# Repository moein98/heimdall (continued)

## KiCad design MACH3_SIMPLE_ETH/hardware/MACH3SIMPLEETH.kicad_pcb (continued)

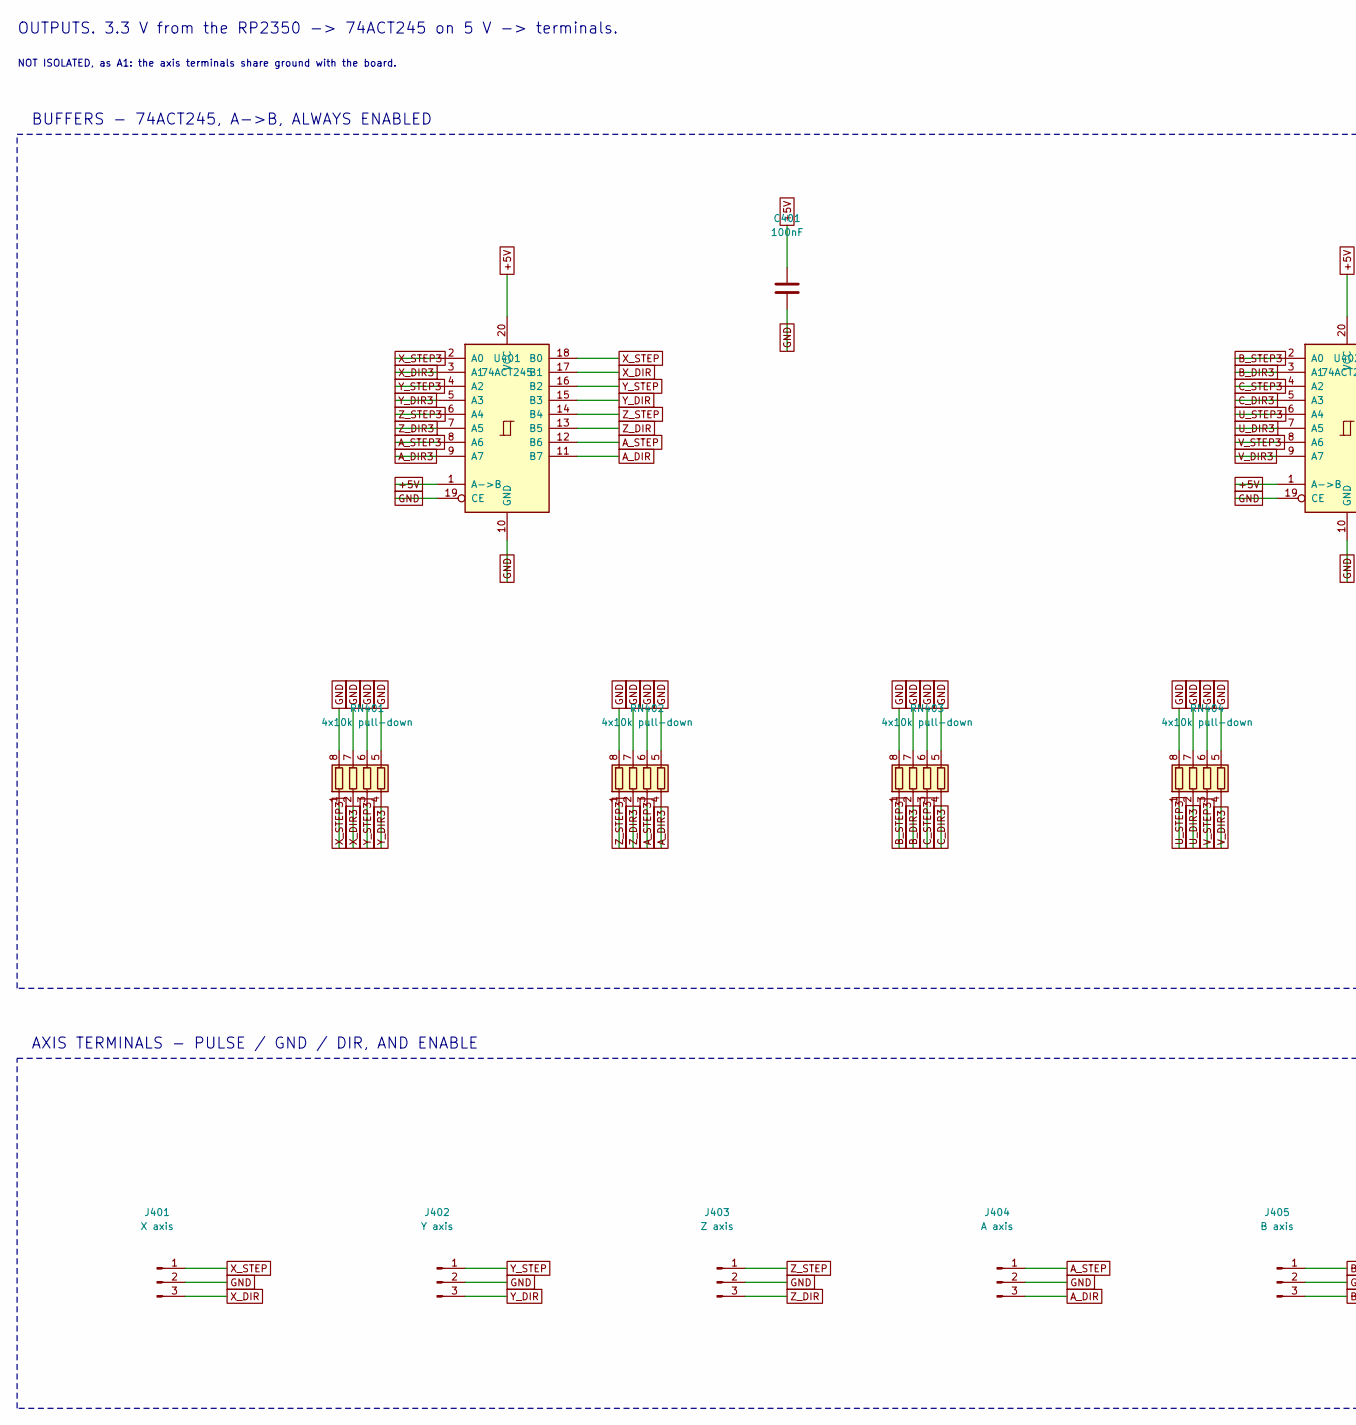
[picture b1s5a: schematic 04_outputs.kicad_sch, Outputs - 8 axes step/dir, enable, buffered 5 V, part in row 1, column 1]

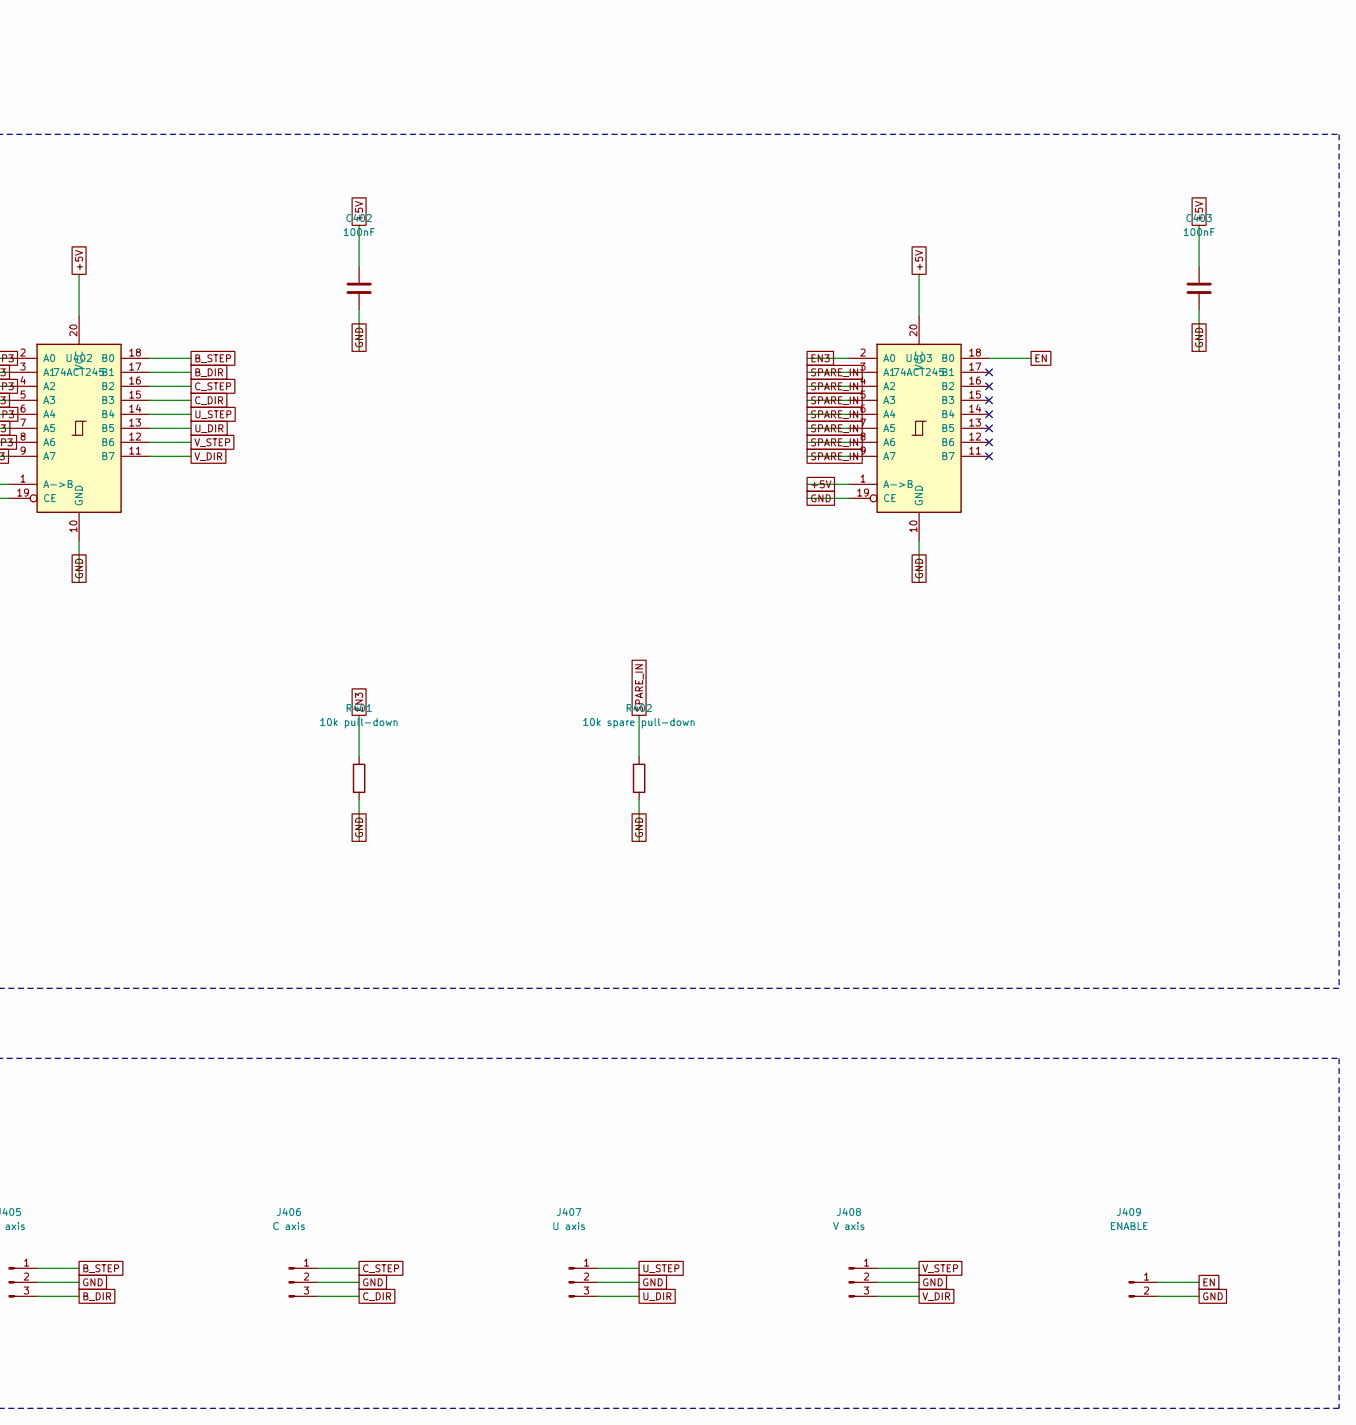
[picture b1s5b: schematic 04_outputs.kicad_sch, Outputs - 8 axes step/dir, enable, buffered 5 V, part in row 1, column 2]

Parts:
C401, C402, C403: 100nF; C_0603_1608Metric
J401: X axis; TerminalBlock_Phoenix_MKDS-1,5-3_1x03_P5.00mm_Horizontal
J402: Y axis; TerminalBlock_Phoenix_MKDS-1,5-3_1x03_P5.00mm_Horizontal
J403: Z axis; TerminalBlock_Phoenix_MKDS-1,5-3_1x03_P5.00mm_Horizontal
J404: A axis; TerminalBlock_Phoenix_MKDS-1,5-3_1x03_P5.00mm_Horizontal
J405: B axis; TerminalBlock_Phoenix_MKDS-1,5-3_1x03_P5.00mm_Horizontal
J406: C axis; TerminalBlock_Phoenix_MKDS-1,5-3_1x03_P5.00mm_Horizontal
J407: U axis; TerminalBlock_Phoenix_MKDS-1,5-3_1x03_P5.00mm_Horizontal
J408: V axis; TerminalBlock_Phoenix_MKDS-1,5-3_1x03_P5.00mm_Horizontal
J409: ENABLE; TerminalBlock_Phoenix_MKDS-1,5-2_1x02_P5.00mm_Horizontal
R401: 10k pull-down; R_0603_1608Metric
R402: 10k spare pull-down; R_0603_1608Metric
RN401, RN402, RN403, RN404: 4x10k pull-down; R_Array_Convex_4x0603
U401, U402, U403: 74ACT245; SOIC-20W_7.5x12.8mm_P1.27mm

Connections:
+5V: C401.1, C402.1, C403.1, U401.1 (A->B), U401.20 (VCC), U402.1 (A->B), U402.20 (VCC), U403.1 (A->B), U403.20 (VCC); also elsewhere on the board
A_DIR: J404.3, U401.11 (B7)
A_DIR3: RN402.4 (R4.1), U401.9 (A7); also elsewhere on the board
A_STEP: J404.1, U401.12 (B6)
A_STEP3: RN402.3 (R3.1), U401.8 (A6); also elsewhere on the board
B_DIR: J405.3, U402.17 (B1)
B_DIR3: RN403.2 (R2.1), U402.3 (A1); also elsewhere on the board
B_STEP: J405.1, U402.18 (B0)
B_STEP3: RN403.1 (R1.1), U402.2 (A0); also elsewhere on the board
C_DIR: J406.3, U402.15 (B3)
C_DIR3: RN403.4 (R4.1), U402.5 (A3); also elsewhere on the board
C_STEP: J406.1, U402.16 (B2)
C_STEP3: RN403.3 (R3.1), U402.4 (A2); also elsewhere on the board
EN: J409.1, U403.18 (B0)
EN3: R401.1, U403.2 (A0); also elsewhere on the board
GND: C401.2, C402.2, C403.2, J401.2, J402.2, J403.2, J404.2, J405.2, J406.2, J407.2, J408.2, J409.2, R401.2, R402.2, RN401.5 (R4.2), RN401.6 (R3.2), RN401.7 (R2.2), RN401.8 (R1.2), RN402.5 (R4.2), RN402.6 (R3.2), RN402.7 (R2.2), RN402.8 (R1.2), RN403.5 (R4.2), RN403.6 (R3.2), RN403.7 (R2.2), RN403.8 (R1.2), RN404.5 (R4.2), RN404.6 (R3.2), RN404.7 (R2.2), RN404.8 (R1.2), U401.10 (GND), U401.19 (CE), U402.10 (GND), U402.19 (CE), U403.10 (GND), U403.19 (CE); also elsewhere on the board
SPARE_IN: R402.1, U403.3 (A1), U403.4 (A2), U403.5 (A3), U403.6 (A4), U403.7 (A5), U403.8 (A6), U403.9 (A7)
U_DIR: J407.3, U402.13 (B5)
U_DIR3: RN404.2 (R2.1), U402.7 (A5); also elsewhere on the board
U_STEP: J407.1, U402.14 (B4)
U_STEP3: RN404.1 (R1.1), U402.6 (A4); also elsewhere on the board
V_DIR: J408.3, U402.11 (B7)
V_DIR3: RN404.4 (R4.1), U402.9 (A7); also elsewhere on the board
V_STEP: J408.1, U402.12 (B6)
V_STEP3: RN404.3 (R3.1), U402.8 (A6); also elsewhere on the board
X_DIR: J401.3, U401.17 (B1)
X_DIR3: RN401.2 (R2.1), U401.3 (A1); also elsewhere on the board
X_STEP: J401.1, U401.18 (B0)
X_STEP3: RN401.1 (R1.1), U401.2 (A0); also elsewhere on the board
Y_DIR: J402.3, U401.15 (B3)
Y_DIR3: RN401.4 (R4.1), U401.5 (A3); also elsewhere on the board
Y_STEP: J402.1, U401.16 (B2)
Y_STEP3: RN401.3 (R3.1), U401.4 (A2); also elsewhere on the board
Z_DIR: J403.3, U401.13 (B5)
Z_DIR3: RN402.2 (R2.1), U401.7 (A5); also elsewhere on the board
Z_STEP: J403.1, U401.14 (B4)
Z_STEP3: RN402.1 (R1.1), U401.6 (A4); also elsewhere on the board

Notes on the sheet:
OUTPUTS. 3.3 V from the RP2350 -> 74ACT245 on 5 V -> terminals.
NOT ISOLATED, as A1: the axis terminals share ground with the board.
BUFFERS - 74ACT245, A->B, ALWAYS ENABLED
AXIS TERMINALS - PULSE / GND / DIR, AND ENABLE

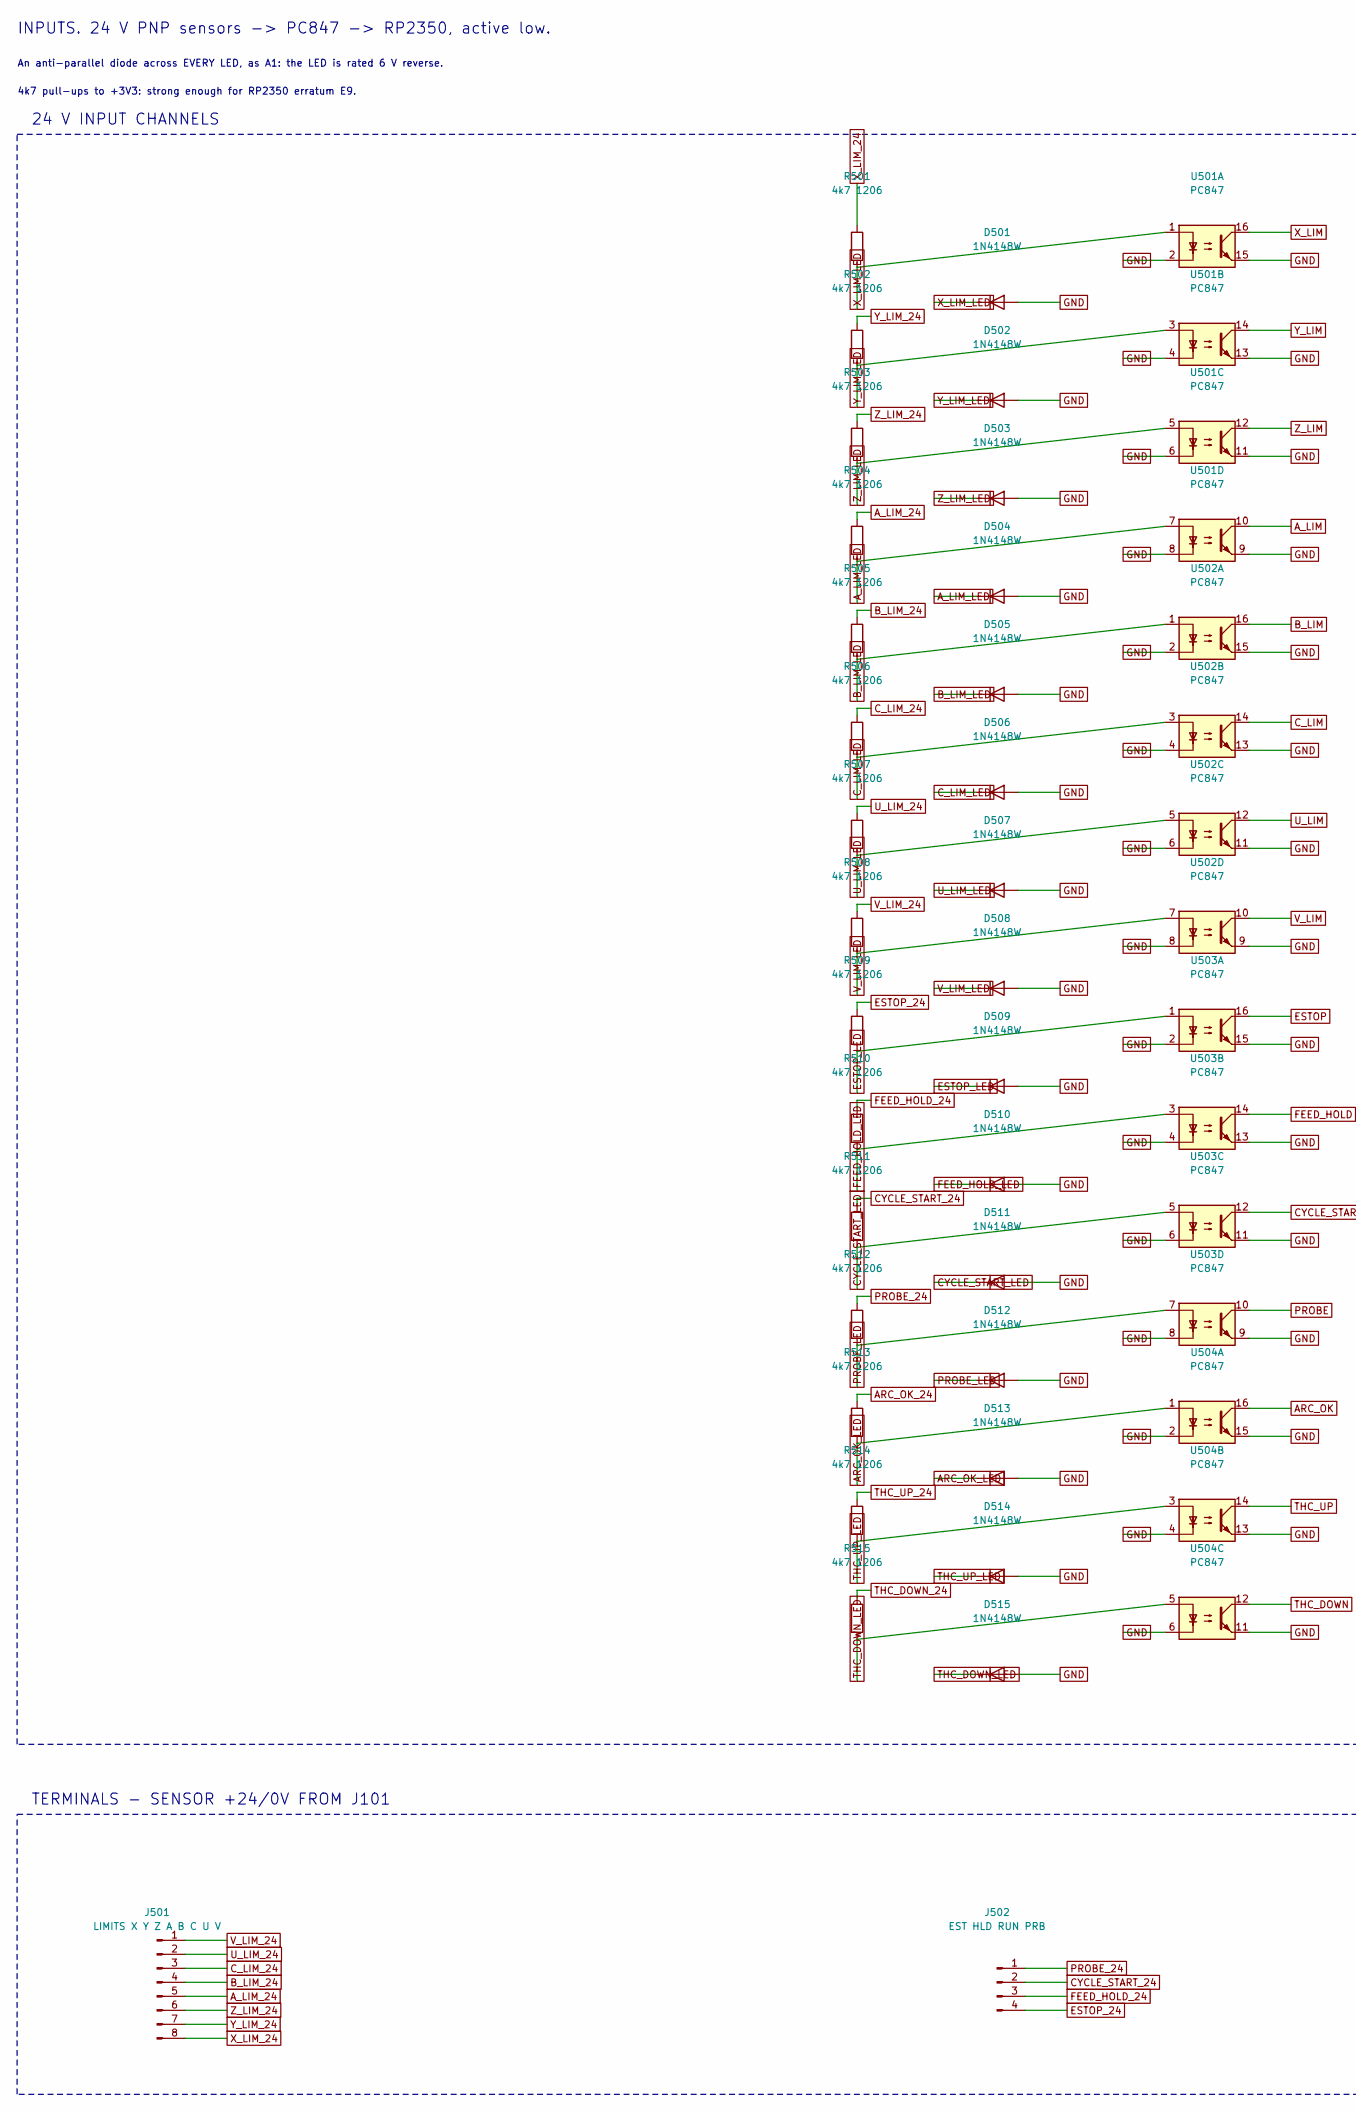
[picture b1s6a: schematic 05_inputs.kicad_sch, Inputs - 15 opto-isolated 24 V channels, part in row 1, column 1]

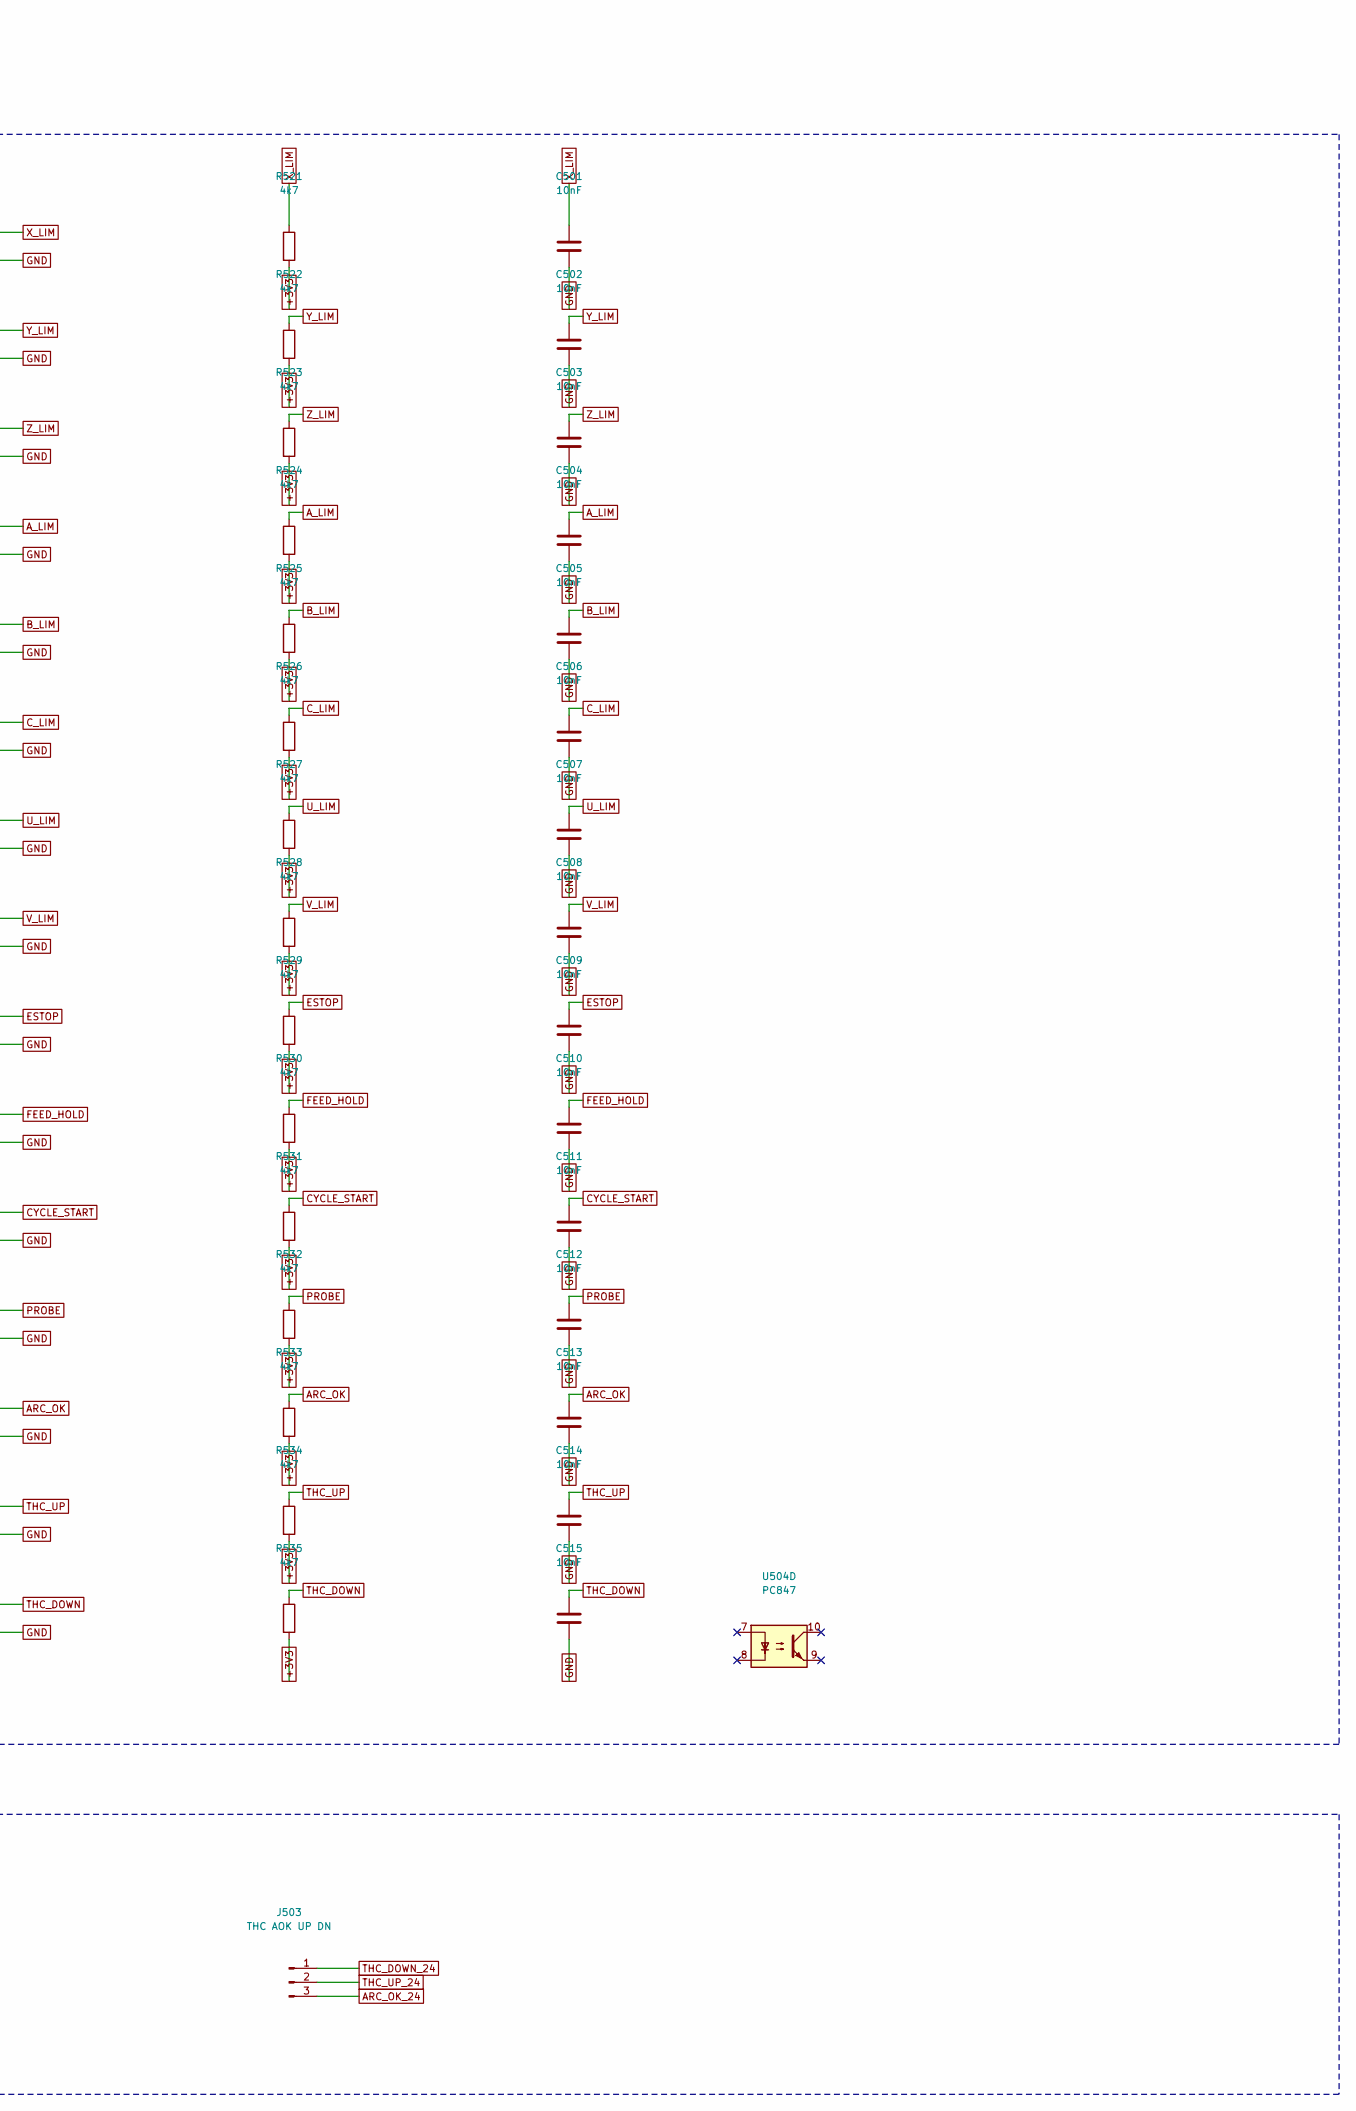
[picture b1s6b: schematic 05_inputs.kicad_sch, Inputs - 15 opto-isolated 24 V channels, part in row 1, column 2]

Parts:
C501, C502, C503, C504, C505, C506, C507, C508, C509, C510, C511, C512, C513, C514, C515: 10nF; C_0603_1608Metric
D501, D502, D503, D504, D505, D506, D507, D508, D509, D510, D511, D512, D513, D514, D515: 1N4148W; D_SOD-123
J501: LIMITS X Y Z A B C U V; TerminalBlock_Phoenix_MKDS-1,5-8_1x08_P5.00mm_Horizontal
J502: EST HLD RUN PRB; TerminalBlock_Phoenix_MKDS-1,5-4_1x04_P5.00mm_Horizontal
J503: THC AOK UP DN; TerminalBlock_Phoenix_MKDS-1,5-3_1x03_P5.00mm_Horizontal
R501, R502, R503, R504, R505, R506, R507, R508, R509, R510, R511, R512, R513, R514, R515: 4k7 1206; R_1206_3216Metric
R521, R522, R523, R524, R525, R526, R527, R528, R529, R530, R531, R532, R533, R534, R535: 4k7; R_0603_1608Metric
U501, U502, U503, U504: PC847; SMDIP-16_W9.53mm

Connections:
+3V3: R521.2, R522.2, R523.2, R524.2, R525.2, R526.2, R527.2, R528.2, R529.2, R530.2, R531.2, R532.2, R533.2, R534.2, R535.2; also elsewhere on the board
ARC_OK: C513.1, R533.1, U504.16; also elsewhere on the board
ARC_OK_24: J503.3, R513.1
ARC_OK_LED: D513.1 (K), R513.2, U504.1
A_LIM: C504.1, R524.1, U501.10; also elsewhere on the board
A_LIM_24: J501.5, R504.1
A_LIM_LED: D504.1 (K), R504.2, U501.7
B_LIM: C505.1, R525.1, U502.16; also elsewhere on the board
B_LIM_24: J501.4, R505.1
B_LIM_LED: D505.1 (K), R505.2, U502.1
CYCLE_START: C511.1, R531.1, U503.12; also elsewhere on the board
CYCLE_START_24: J502.2, R511.1
CYCLE_START_LED: D511.1 (K), R511.2, U503.5
C_LIM: C506.1, R526.1, U502.14; also elsewhere on the board
C_LIM_24: J501.3, R506.1
C_LIM_LED: D506.1 (K), R506.2, U502.3
ESTOP: C509.1, R529.1, U503.16; also elsewhere on the board
ESTOP_24: J502.4, R509.1
ESTOP_LED: D509.1 (K), R509.2, U503.1
FEED_HOLD: C510.1, R530.1, U503.14; also elsewhere on the board
FEED_HOLD_24: J502.3, R510.1
FEED_HOLD_LED: D510.1 (K), R510.2, U503.3
GND: C501.2, C502.2, C503.2, C504.2, C505.2, C506.2, C507.2, C508.2, C509.2, C510.2, C511.2, C512.2, C513.2, C514.2, C515.2, D501.2 (A), D502.2 (A), D503.2 (A), D504.2 (A), D505.2 (A), D506.2 (A), D507.2 (A), D508.2 (A), D509.2 (A), D510.2 (A), D511.2 (A), D512.2 (A), D513.2 (A), D514.2 (A), D515.2 (A), U501.2, U501.4, U501.6, U501.8, U501.9, U501.11, U501.13, U501.15, U502.2, U502.4, U502.6, U502.8, U502.9, U502.11, U502.13, U502.15, U503.2, U503.4, U503.6, U503.8, U503.9, U503.11, U503.13, U503.15, U504.2, U504.4, U504.6, U504.11, U504.13, U504.15; also elsewhere on the board
PROBE: C512.1, R532.1, U503.10; also elsewhere on the board
PROBE_24: J502.1, R512.1
PROBE_LED: D512.1 (K), R512.2, U503.7
THC_DOWN: C515.1, R535.1, U504.12; also elsewhere on the board
THC_DOWN_24: J503.1, R515.1
THC_DOWN_LED: D515.1 (K), R515.2, U504.5
THC_UP: C514.1, R534.1, U504.14; also elsewhere on the board
THC_UP_24: J503.2, R514.1
THC_UP_LED: D514.1 (K), R514.2, U504.3
U_LIM: C507.1, R527.1, U502.12; also elsewhere on the board
U_LIM_24: J501.2, R507.1
U_LIM_LED: D507.1 (K), R507.2, U502.5
V_LIM: C508.1, R528.1, U502.10; also elsewhere on the board
V_LIM_24: J501.1, R508.1
V_LIM_LED: D508.1 (K), R508.2, U502.7
X_LIM: C501.1, R521.1, U501.16; also elsewhere on the board
X_LIM_24: J501.8, R501.1
X_LIM_LED: D501.1 (K), R501.2, U501.1
Y_LIM: C502.1, R522.1, U501.14; also elsewhere on the board
Y_LIM_24: J501.7, R502.1
Y_LIM_LED: D502.1 (K), R502.2, U501.3
Z_LIM: C503.1, R523.1, U501.12; also elsewhere on the board
Z_LIM_24: J501.6, R503.1
Z_LIM_LED: D503.1 (K), R503.2, U501.5

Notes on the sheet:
INPUTS. 24 V PNP sensors -> PC847 -> RP2350, active low.
An anti-parallel diode across EVERY LED, as A1: the LED is rated 6 V reverse.
4k7 pull-ups to +3V3: strong enough for RP2350 erratum E9.
24 V INPUT CHANNELS
TERMINALS - SENSOR +24/0V FROM J101

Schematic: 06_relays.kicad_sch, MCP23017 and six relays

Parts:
C601: 100nF; C_0603_1608Metric
D601: STATUS; LED_0603_1608Metric
D611, D612, D613, D614, D615, D616: 1N4148W flyback; D_SOD-123
D621: KA; LED_0603_1608Metric
D622: KB; LED_0603_1608Metric
D623: KC; LED_0603_1608Metric
D624: KD; LED_0603_1608Metric
D625: KE; LED_0603_1608Metric
D626: KF; LED_0603_1608Metric
J601: EXPANSION; IDC-Header_2x05_P2.54mm_Vertical
J611: Relay A; TerminalBlock_Phoenix_MKDS-1,5-3_1x03_P5.00mm_Horizontal
J612: Relay B; TerminalBlock_Phoenix_MKDS-1,5-3_1x03_P5.00mm_Horizontal
J613: Relay C; TerminalBlock_Phoenix_MKDS-1,5-3_1x03_P5.00mm_Horizontal
J614: Relay D; TerminalBlock_Phoenix_MKDS-1,5-3_1x03_P5.00mm_Horizontal
J615: Relay E; TerminalBlock_Phoenix_MKDS-1,5-3_1x03_P5.00mm_Horizontal
J616: Relay F; TerminalBlock_Phoenix_MKDS-1,5-3_1x03_P5.00mm_Horizontal
K601, K602, K603, K604, K605, K606: JQC-3FF-024-1Z; Relay_SPDT_Hongfa_JQC-3FF_0XX-1Z
Q601, Q602, Q603, Q604, Q605, Q606: AO3400A; SOT-23
R601, R602: 4.7k; R_0603_1608Metric
R603, R621, R622, R623, R624, R625, R626: 1k; R_0603_1608Metric
R604, R605, R606, R607, R608, R609, R610, R611, R631, R632, R633, R634, R635, R636, R641, R642, R643, R644, R645, R646: 10k; R_0603_1608Metric
U601: MCP23017-E/SO; SOIC-28W_7.5x17.9mm_P1.27mm

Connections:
+3V3: C601.1, J601.9, R601.1, R602.1, R604.2, R605.2, R606.2, R607.2, R608.2, R609.2, R610.2, R611.2, U601.9 (V_{DD}); also elsewhere on the board
EXP_IN0: J601.1, R604.1, U601.1 (GPB0)
EXP_IN1: J601.2, R605.1, U601.2 (GPB1)
EXP_IN2: J601.3, R606.1, U601.3 (GPB2)
EXP_IN3: J601.4, R607.1, U601.4 (GPB3)
EXP_IN4: J601.5, R608.1, U601.5 (GPB4)
EXP_IN5: J601.6, R609.1, U601.6 (GPB5)
EXP_IN6: J601.7, R610.1, U601.7 (GPB6)
EXP_IN7: J601.8, R611.1, U601.8 (GPB7)
GND: C601.2, D601.1 (K), J601.10, Q601.2 (S), Q602.2 (S), Q603.2 (S), Q604.2 (S), Q605.2 (S), Q606.2 (S), R631.2, R632.2, R633.2, R634.2, R635.2, R636.2, U601.10 (V_{SS}), U601.15 (A0), U601.16 (A1), U601.17 (A2); also elsewhere on the board
I2C_SCL: R602.2, U601.12 (SCK); also elsewhere on the board
I2C_SDA: R601.2, U601.13 (SDA); also elsewhere on the board
KA_COM: J611.2, K601.11
KA_NC: J611.3, K601.12
KA_NO: J611.1, K601.14
KB_COM: J612.2, K602.11
KB_NC: J612.3, K602.12
KB_NO: J612.1, K602.14
KC_COM: J613.2, K603.11
KC_NC: J613.3, K603.12
KC_NO: J613.1, K603.14
KD_COM: J614.2, K604.11
KD_NC: J614.3, K604.12
KD_NO: J614.1, K604.14
KE_COM: J615.2, K605.11
KE_NC: J615.3, K605.12
KE_NO: J615.1, K605.14
KF_COM: J616.2, K606.11
KF_NC: J616.3, K606.12
KF_NO: J616.1, K606.14
NRST: U601.18 (~RESET); also elsewhere on the board
unnamed: D621.2 (A), R641.2
unnamed: D622.2 (A), R642.2
unnamed: D623.2 (A), R643.2
unnamed: D624.2 (A), R644.2
unnamed: D625.2 (A), R645.2
unnamed: D626.2 (A), R646.2
unnamed: Q601.1 (G), R621.2
unnamed: Q602.1 (G), R622.2
unnamed: Q603.1 (G), R623.2
unnamed: Q604.1 (G), R624.2
unnamed: Q605.1 (G), R625.2
unnamed: Q606.1 (G), R626.2
RELC_A: D611.2 (A), D621.1 (K), K601.A2, Q601.3 (D)
RELC_B: D612.2 (A), D622.1 (K), K602.A2, Q602.3 (D)
RELC_C: D613.2 (A), D623.1 (K), K603.A2, Q603.3 (D)
RELC_D: D614.2 (A), D624.1 (K), K604.A2, Q604.3 (D)
RELC_E: D615.2 (A), D625.1 (K), K605.A2, Q605.3 (D)
RELC_F: D616.2 (A), D626.1 (K), K606.A2, Q606.3 (D)
REL_A: R621.1, R631.1, U601.21 (GPA0)
REL_B: R622.1, R632.1, U601.22 (GPA1)
REL_C: R623.1, R633.1, U601.23 (GPA2)
REL_D: R624.1, R634.1, U601.24 (GPA3)
REL_E: R625.1, R635.1, U601.25 (GPA4)
REL_F: R626.1, R636.1, U601.26 (GPA5)
SP_AUX_IN: U601.27 (GPA6); also elsewhere on the board
STATUS_LED: R603.1, U601.28 (GPA7)
STATUS_LED_A: D601.2 (A), R603.2
V24: D611.1 (K), D612.1 (K), D613.1 (K), D614.1 (K), D615.1 (K), D616.1 (K), K601.A1, K602.A1, K603.A1, K604.A1, K605.A1, K606.A1, R641.1, R642.1, R643.1, R644.1, R645.1, R646.1; also elsewhere on the board

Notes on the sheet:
RELAYS. MCP23017 (I2C 0x20) -> AO3400A -> 24 V relay coils.
G-code M62/M63 P<n> switch them, synchronised with motion; M64/M65 at once.
MCP23017 AND EXPANSION HEADER
SIX RELAYS - 24 V COILS ONLY, AS A1

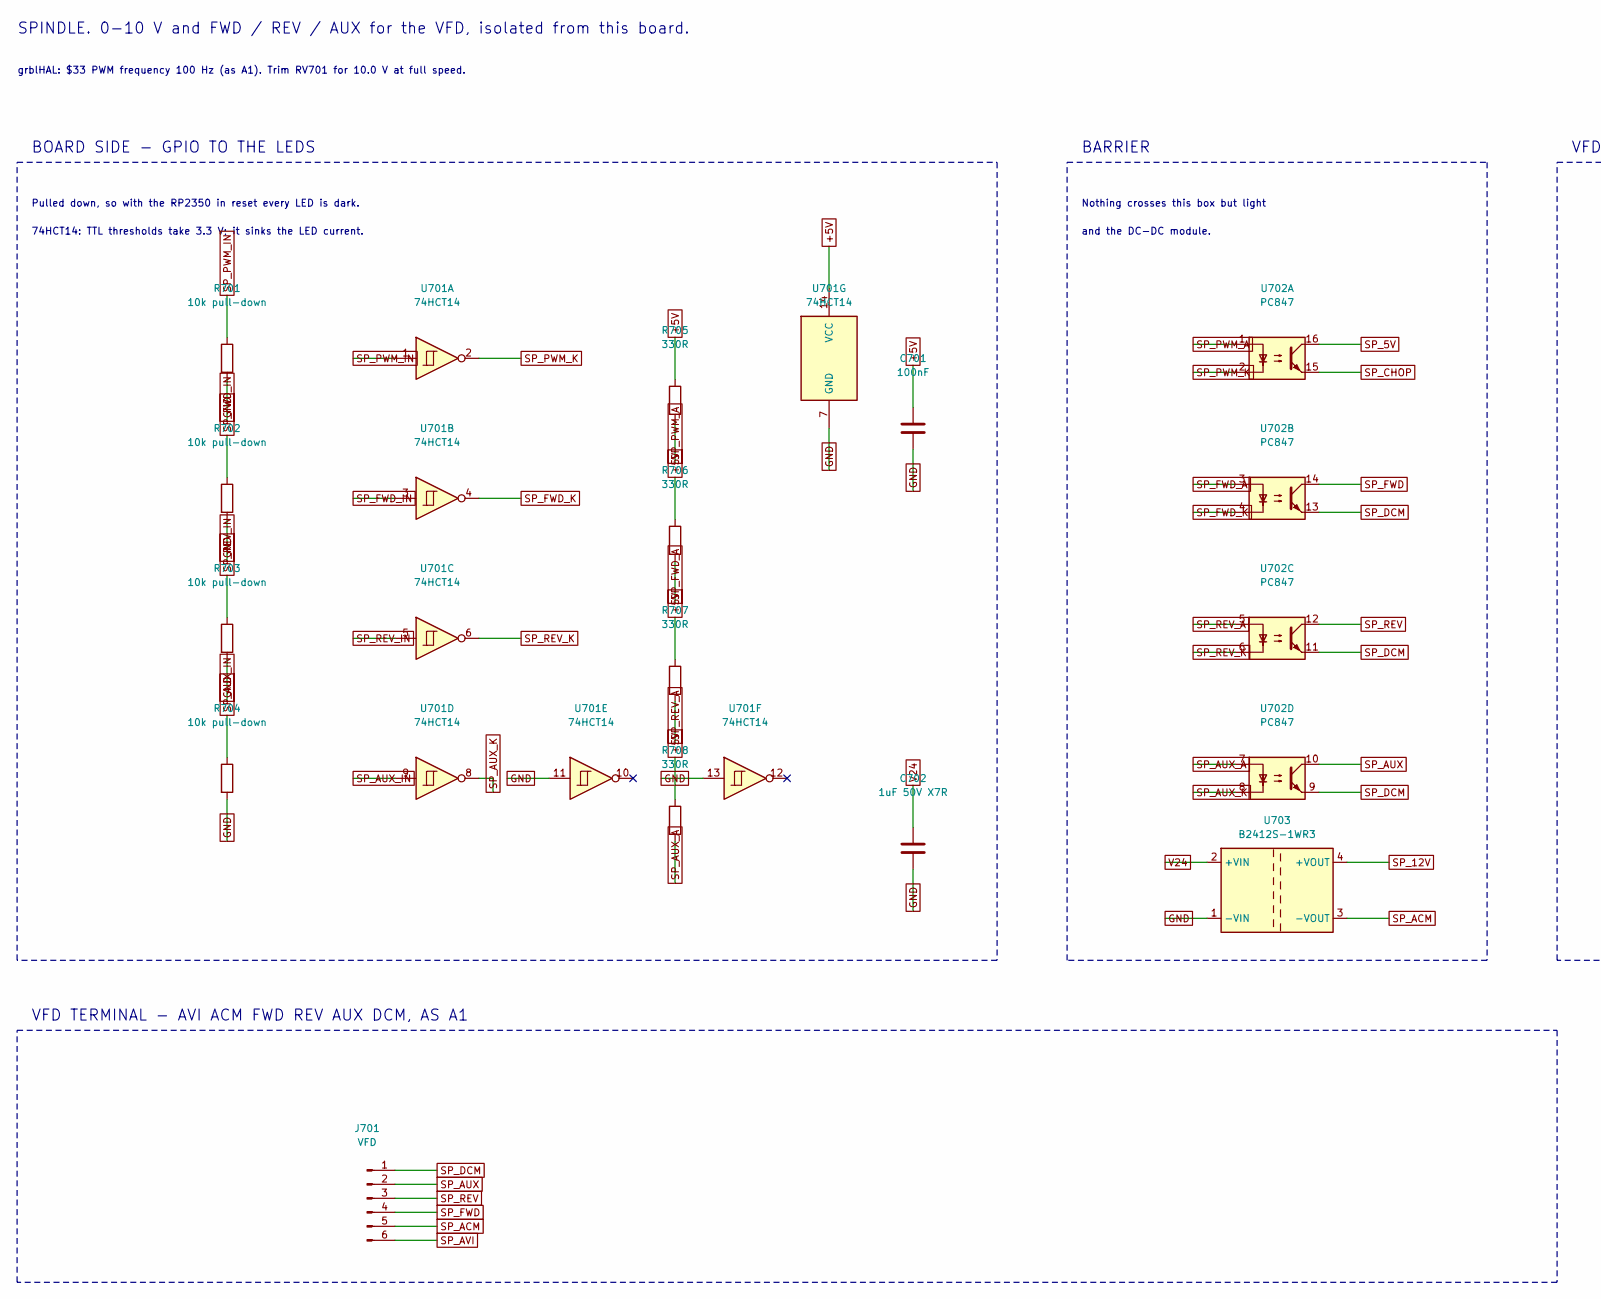
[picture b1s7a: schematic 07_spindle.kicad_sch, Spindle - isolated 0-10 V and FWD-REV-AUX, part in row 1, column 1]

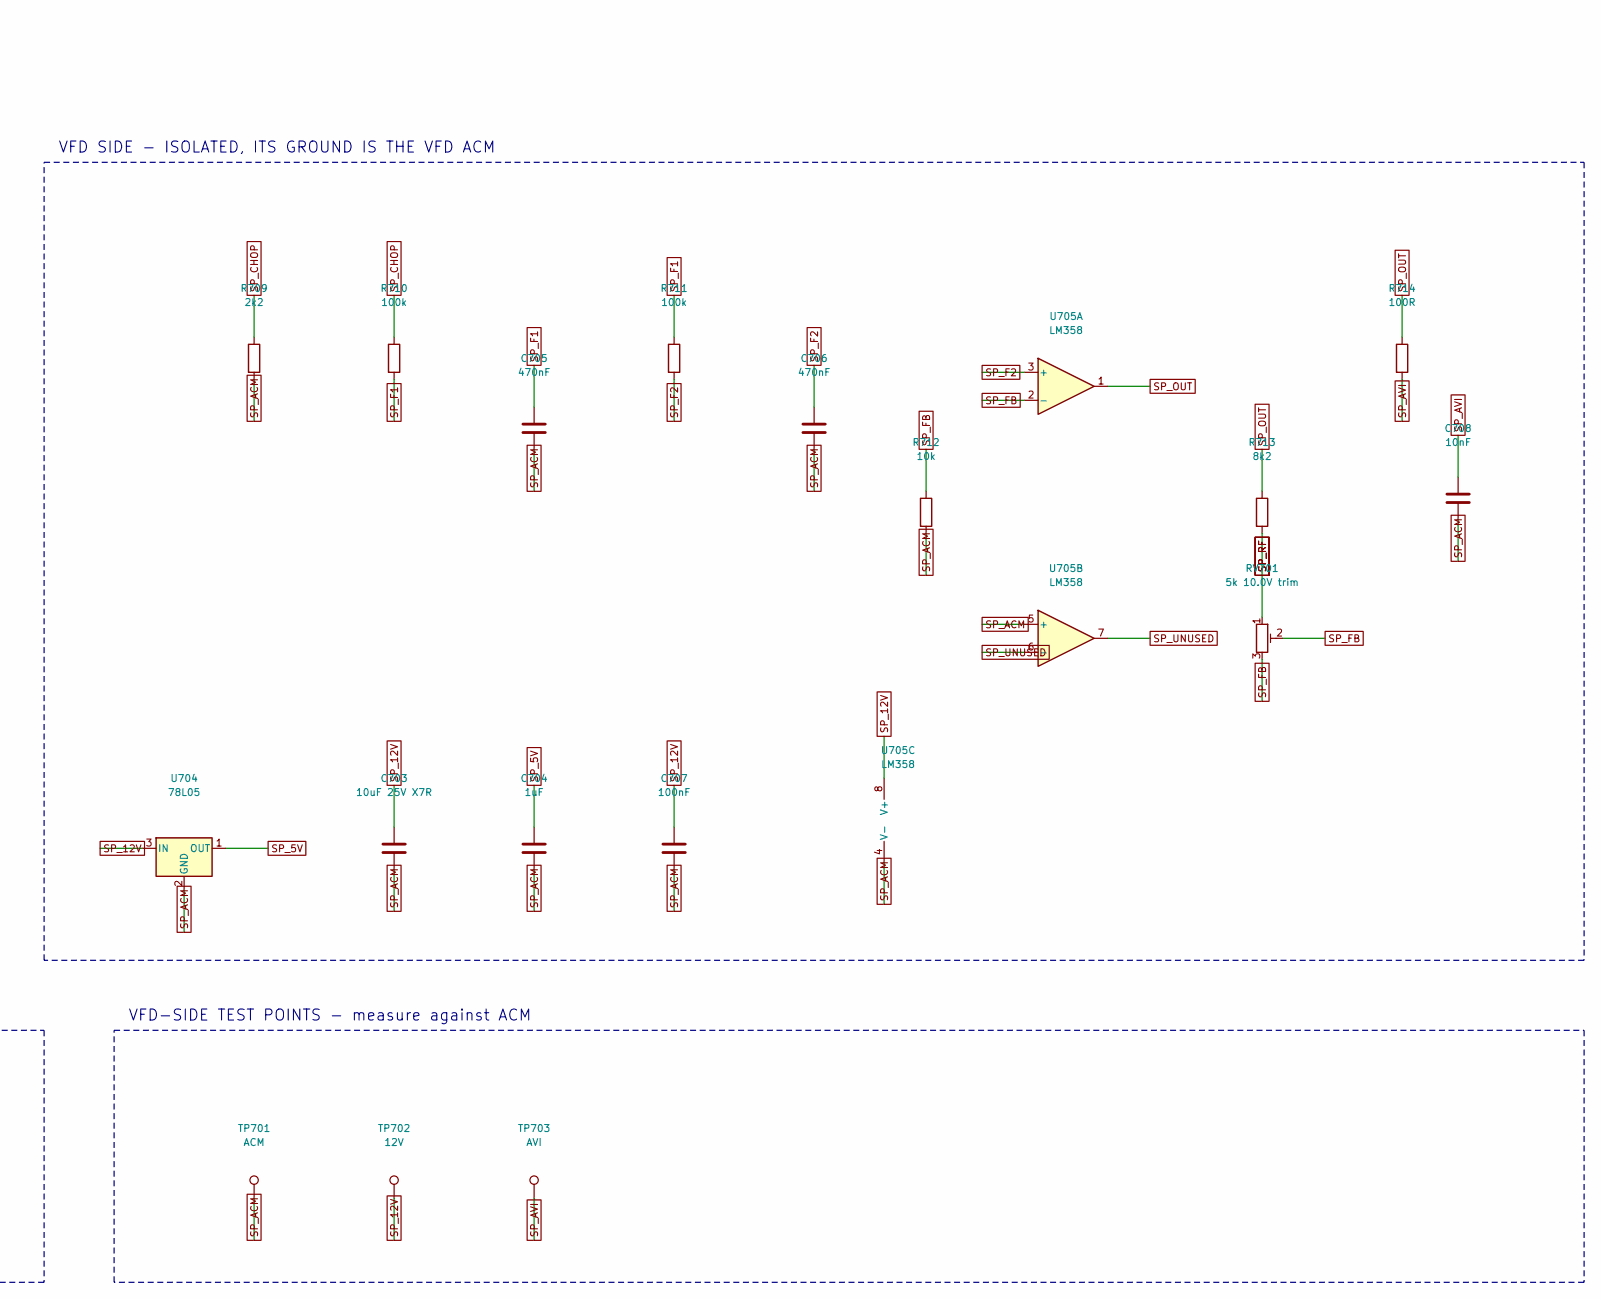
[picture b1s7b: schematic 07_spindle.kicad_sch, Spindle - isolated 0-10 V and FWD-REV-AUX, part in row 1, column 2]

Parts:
C701, C707: 100nF; C_0603_1608Metric
C702: 1uF 50V X7R; C_1206_3216Metric
C703: 10uF 25V X7R; C_1206_3216Metric
C704: 1uF; C_0603_1608Metric
C705, C706: 470nF; C_0603_1608Metric
C708: 10nF; C_0603_1608Metric
J701: VFD; TerminalBlock_Phoenix_MKDS-1,5-6_1x06_P5.00mm_Horizontal
R701, R702, R703, R704: 10k pull-down; R_0603_1608Metric
R705, R706, R707, R708: 330R; R_0603_1608Metric
R709: 2k2; R_0603_1608Metric
R710, R711: 100k; R_0603_1608Metric
R712: 10k; R_0603_1608Metric
R713: 8k2; R_0603_1608Metric
R714: 100R; R_0603_1608Metric
RV701: 5k 10.0V trim; Potentiometer_Bourns_3296W_Vertical
TP701: ACM; TestPoint_THTPad_D2.0mm_Drill1.0mm
TP702: 12V; TestPoint_THTPad_D2.0mm_Drill1.0mm
TP703: AVI; TestPoint_THTPad_D2.0mm_Drill1.0mm
U701: 74HCT14; SOIC-14_3.9x8.7mm_P1.27mm
U702: PC847; SMDIP-16_W9.53mm
U703: B2412S-1WR3; Converter_DCDC_Murata_CRE1xxxxxxSC_THT
U704: 78L05; SOT-89-3
U705: LM358; SOIC-8_3.9x4.9mm_P1.27mm

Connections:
+5V: C701.1, R705.1, R706.1, R707.1, R708.1, U701.14 (VCC); also elsewhere on the board
GND: C701.2, C702.2, R701.2, R702.2, R703.2, R704.2, U701.7 (GND), U701.11, U701.13, U703.1 (-VIN); also elsewhere on the board
SP_5V: C704.1, U702.16, U704.1 (OUT)
SP_12V: C703.1, C707.1, TP702.1, U703.4 (+VOUT), U704.3 (IN), U705.8 (V+)
SP_ACM: C703.2, C704.2, C705.2, C706.2, C707.2, C708.2, J701.5, R709.2, R712.2, TP701.1, U703.3 (-VOUT), U704.2 (GND), U705.4 (V-), U705.5 (+)
SP_AUX: J701.2, U702.10
SP_AUX_A: R708.2, U702.7
SP_AUX_IN: R704.1, U701.9; also elsewhere on the board
SP_AUX_K: U701.8, U702.8
SP_AVI: C708.1, J701.6, R714.2, TP703.1
SP_CHOP: R709.1, R710.1, U702.15
SP_DCM: J701.1, U702.9, U702.11, U702.13
SP_F1: C705.1, R710.2, R711.1
SP_F2: C706.1, R711.2, U705.3 (+)
SP_FB: R712.1, RV701.2, RV701.3, U705.2 (-)
SP_FWD: J701.4, U702.14
SP_FWD_A: R706.2, U702.3
SP_FWD_IN: R702.1, U701.3; also elsewhere on the board
SP_FWD_K: U701.4, U702.4
SP_OUT: R713.1, R714.1, U705.1
SP_PWM_A: R705.2, U702.1
SP_PWM_IN: R701.1, U701.1; also elsewhere on the board
SP_PWM_K: U701.2, U702.2
SP_REV: J701.3, U702.12
SP_REV_A: R707.2, U702.5
SP_REV_IN: R703.1, U701.5; also elsewhere on the board
SP_REV_K: U701.6, U702.6
SP_RF: R713.2, RV701.1
SP_UNUSED: U705.6 (-), U705.7
V24: C702.1, U703.2 (+VIN); also elsewhere on the board

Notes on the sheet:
SPINDLE. 0-10 V and FWD / REV / AUX for the VFD, isolated from this board.
grblHAL: $33 PWM frequency 100 Hz (as A1). Trim RV701 for 10.0 V at full speed.
BOARD SIDE - GPIO TO THE LEDS
Pulled down, so with the RP2350 in reset every LED is dark.
74HCT14: TTL thresholds take 3.3 V; it sinks the LED current.
BARRIER
Nothing crosses this box but light
and the DC-DC module.
VFD SIDE - ISOLATED, ITS GROUND IS THE VFD ACM
VFD-SIDE TEST POINTS - measure against ACM
VFD TERMINAL - AVI ACM FWD REV AUX DCM, AS A1
